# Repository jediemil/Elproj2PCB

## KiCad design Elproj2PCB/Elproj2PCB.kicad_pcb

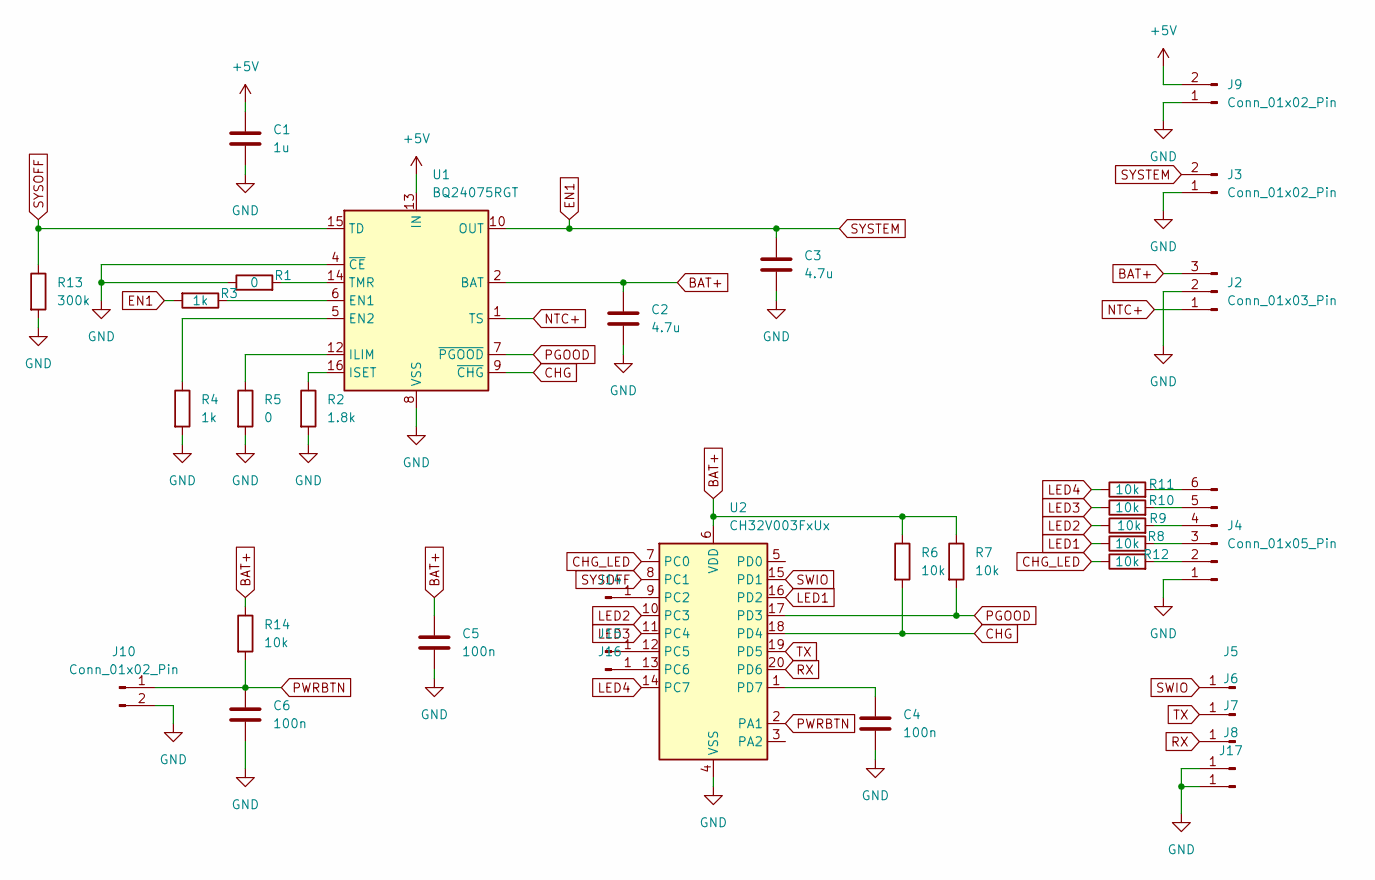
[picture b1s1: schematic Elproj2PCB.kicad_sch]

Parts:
C1: 1u; C_0603_1608Metric
C2, C3: 4.7u; C_0603_1608Metric
C4, C5, C6: 100n; C_0603_1608Metric
J2: Conn_01x03_Pin; PinHeader_1x03_P1.00mm_Vertical
J3, J9, J10: Conn_01x02_Pin; PinHeader_1x02_P1.00mm_Vertical
J4: Conn_01x05_Pin; PinHeader_1x06_P1.00mm_Vertical
J5, J6, J7, J8, J14, J15, J16, J17: Conn_01x01_Pin; TestPoint_Pad_D1.0mm
R1, R5: 0; R_0603_1608Metric
R2: 1.8k; R_0603_1608Metric
R3, R4: 1k; R_0603_1608Metric
R6, R7, R8, R9, R10, R11, R12, R14: 10k; R_0603_1608Metric
R13: 300k; R_0603_1608Metric
U1: BQ24075RGT; VQFN-16-1EP_3x3mm_P0.5mm_EP1.6x1.6mm
U2: CH32V003FxUx; QFN-20-1EP_3x3mm_P0.4mm_EP1.65x1.65mm

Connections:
+5V: C1.1, J9.2, U1.13 (IN)
BAT+: C2.1, C5.1, J2.3, R6.1, R7.1, R14.1, U1.2 (BAT), U1.3 (BAT), U2.6 (VDD)
CHG: R6.2, U1.9 (~CHG), U2.18 (PD4)
CHG_LED: R12.1, U2.7 (PC0)
EN1: C3.1, J3.2, R3.2, U1.10 (OUT), U1.11 (OUT)
GND: C1.2, C2.2, C3.2, C4.2, C5.2, C6.2, J2.2, J3.1, J4.1, J8.1, J9.1, J10.2, J17.1, R1.1, R2.2, R4.2, R5.2, R13.2, U1.4 (~CE), U1.8 (VSS), U1.17 (VSS), U2.4 (VSS), U2.21 (VSS)
LED1: R8.1, U2.16 (PD2)
LED2: R9.1, U2.10 (PC3)
LED3: R10.1, U2.11 (PC4)
LED4: R11.1, U2.14 (PC7)
NTC+: J2.1, U1.1 (TS)
unnamed: J4.2, R12.2
unnamed: J4.3, R8.2
unnamed: J4.4, R9.2
unnamed: J4.5, R10.2
unnamed: J4.6, R11.2
unnamed: J14.1, U2.9 (PC2)
unnamed: J15.1, U2.12 (PC5)
unnamed: J16.1, U2.13 (PC6)
unnamed: R3.1, U1.6 (EN1)
unnamed: R4.1, U1.5 (EN2)
unnamed: R5.1, U1.12 (ILIM)
unnamed: R2.1, U1.16 (ISET)
unnamed: R1.2, U1.14 (TMR)
unnamed: C4.1, U2.1 (PD7)
PGOOD: R7.2, U1.7 (~PGOOD), U2.17 (PD3)
PWRBTN: C6.1, J10.1, R14.2, U2.2 (PA1)
RX: J7.1, U2.20 (PD6)
SWIO: J5.1, U2.15 (PD1)
SYSOFF: R13.1, U1.15 (TD), U2.8 (PC1)
TX: J6.1, U2.19 (PD5)

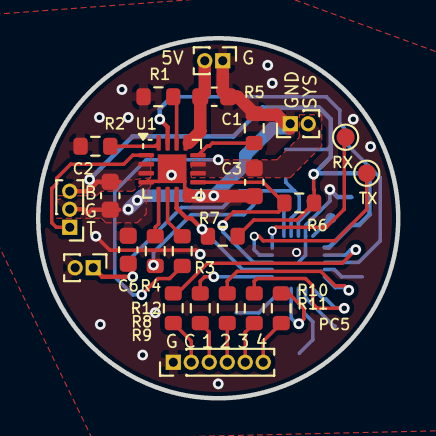
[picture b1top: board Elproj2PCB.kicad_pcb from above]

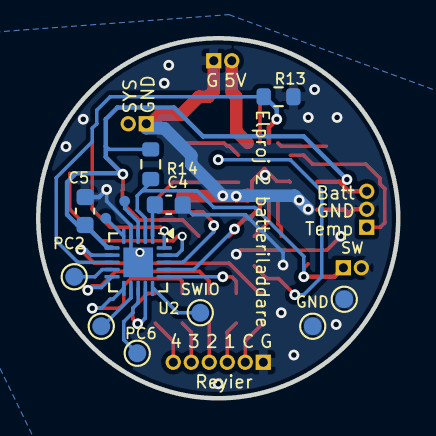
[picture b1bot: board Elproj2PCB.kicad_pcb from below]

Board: 2 copper layers, 20.0 x 20.0 mm, 35 parts (11 on the bottom side), 31 nets.

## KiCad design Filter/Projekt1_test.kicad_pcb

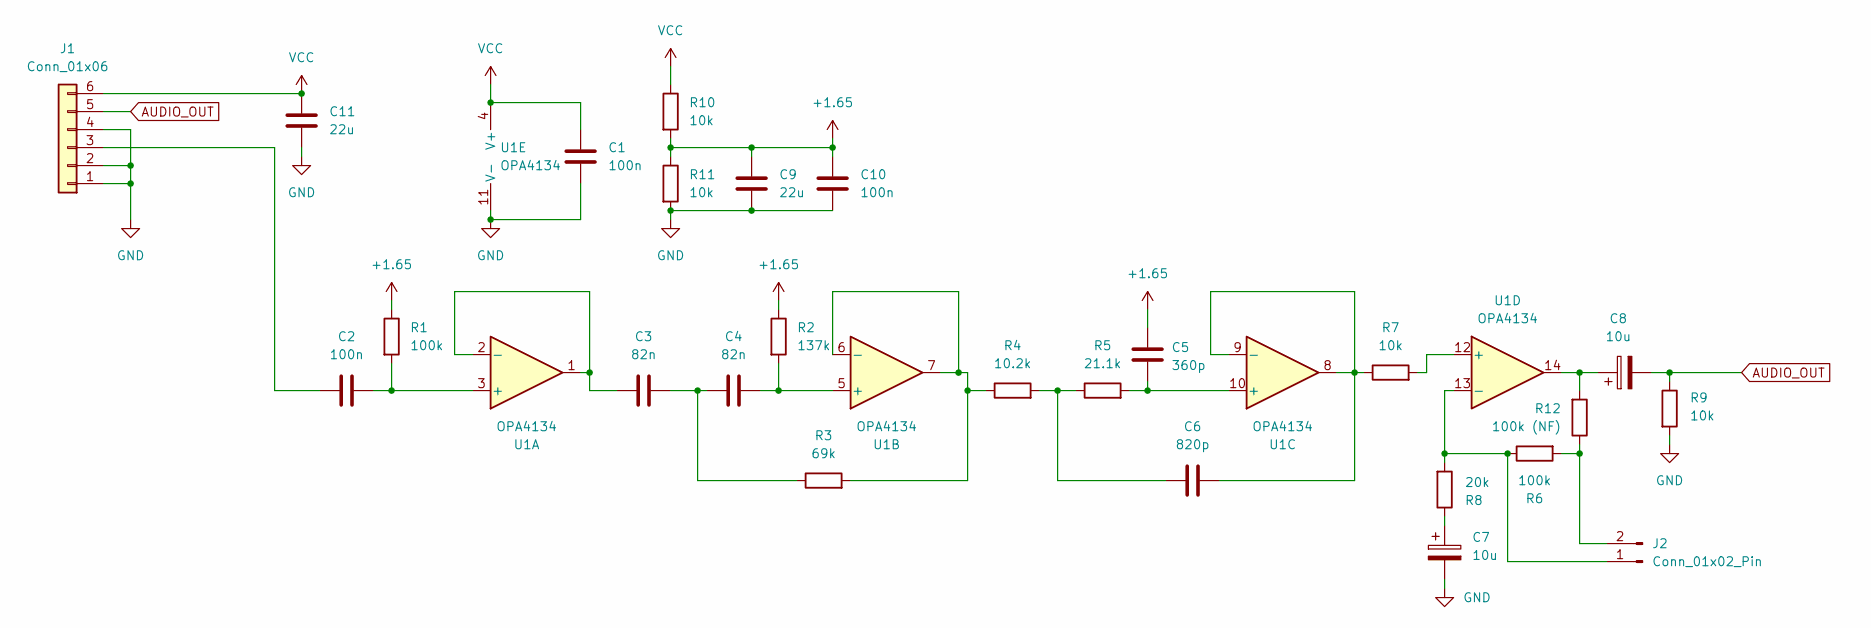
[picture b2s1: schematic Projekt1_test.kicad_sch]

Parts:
C1, C10: 100n; C_0603_1608Metric
C2: 100n; R_1206_3216Metric
C3, C4: 82n; R_1206_3216Metric
C5: 360p; R_1206_3216Metric
C6: 820p; R_1206_3216Metric
C7, C8: 10u; CP_EIA-3216-18_Kemet-A
C9, C11: 22u; C_0805_2012Metric
J1: Conn_01x06; PinHeader_1x06_P1.00mm_Vertical
J2: Conn_01x02_Pin; PinHeader_1x02_P1.00mm_Vertical
R1, R6: 100k; R_0603_1608Metric
R2: 137k; R_0603_1608Metric
R3: 69k; R_0603_1608Metric
R4: 10.2k; R_0603_1608Metric
R5: 21.1k; R_0603_1608Metric
R7, R9, R10, R11: 10k; R_0603_1608Metric
R8: 20k; R_0603_1608Metric
R12: 100k (NF); R_0603_1608Metric
U1: OPA4134; SOIC-14_3.9x8.7mm_P1.27mm

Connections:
+1.65: C5.2, C9.2, C10.2, R1.1, R2.1, R10.2, R11.1
AUDIO_OUT: C8.2, J1.5, R9.1
GND: C1.1, C7.2, C9.1, C10.1, C11.1, J1.1, J1.2, J1.4, R9.2, R11.2, U1.11 (V-)
unnamed: C3.1, C4.2, R3.1
unnamed: C6.2, R4.2, R5.1
unnamed: C7.1, R8.1
unnamed: C8.1, R12.2, U1.14
unnamed: C2.2, J1.3
unnamed: J2.1, R6.1, R8.2, U1.13 (-)
unnamed: J2.2, R6.2, R12.1
unnamed: C2.1, R1.2, U1.3 (+)
unnamed: C3.2, U1.1, U1.2 (-)
unnamed: C4.1, R2.2, U1.5 (+)
unnamed: R3.2, R4.1, U1.6 (-), U1.7
unnamed: C5.1, R5.2, U1.10 (+)
unnamed: C6.1, R7.1, U1.8, U1.9 (-)
unnamed: R7.2, U1.12 (+)
VCC: C1.2, C11.2, J1.6, R10.1, U1.4 (V+)

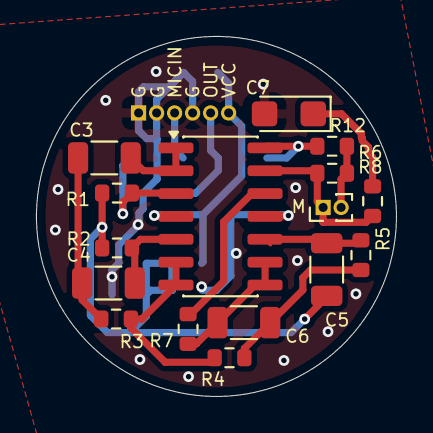
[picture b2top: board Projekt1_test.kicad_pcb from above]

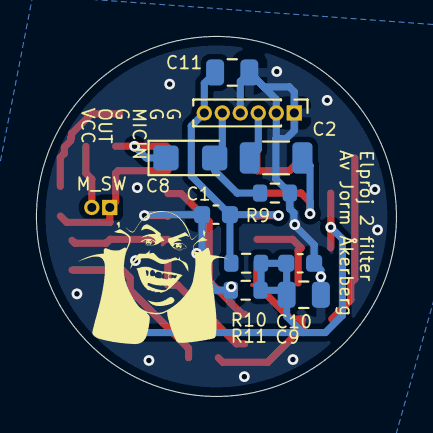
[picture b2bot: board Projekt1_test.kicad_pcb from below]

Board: 4 copper layers, 20.0 x 20.0 mm, 26 parts (10 on the bottom side), 18 nets.

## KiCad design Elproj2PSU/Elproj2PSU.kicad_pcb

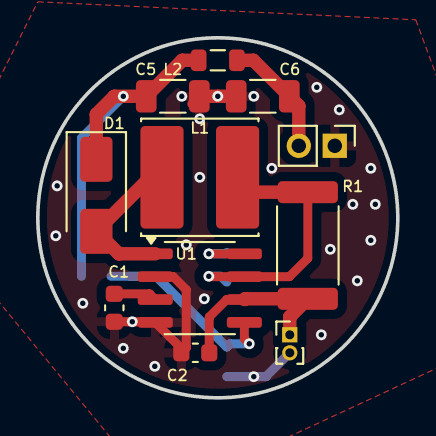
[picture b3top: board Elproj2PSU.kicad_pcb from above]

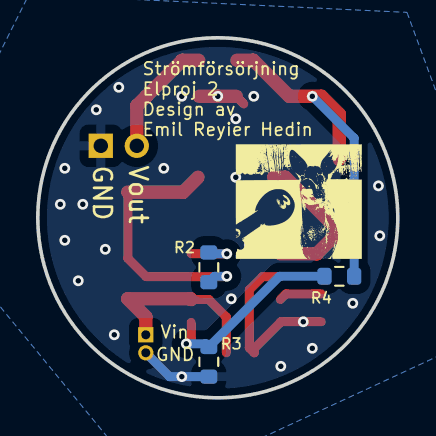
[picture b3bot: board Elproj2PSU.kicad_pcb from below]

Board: 2 copper layers, 20.0 x 20.0 mm, 14 parts (3 on the bottom side), 9 nets.

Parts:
C1: 400p; C_0603_1608Metric
C2: 100n; C_0603_1608Metric
C5, C6: 2.2u; C_1206_3216Metric
D1: D; D_SMA
J1: Conn_01x02_Pin; PinHeader_1x02_P1.00mm_Vertical
J2: Conn_01x02_Pin; PinHeader_1x02_P2.00mm_Vertical
L1: 78u; L_Cenker_CKCS6028
L2: 4.7u; L_0805_2012Metric
R1: 0.8; R_2512_6332Metric
R2: 180; R_0603_1608Metric
R3: 1.5k; R_0603_1608Metric
R4: 56k; R_0603_1608Metric
U1: MC34063AD; SOIC-8_3.9x4.9mm_P1.27mm

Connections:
+48V: C6.1, J2.2, L2.2
+BATT: C2.1, J1.1, R1.1, U1.6 (Vin)
GND: C1.2, C2.2, C5.2, C6.2, J1.2, J2.1, R3.1, U1.2 (SwE), U1.4 (GND)
unnamed: D1.2 (A), L1.2, U1.1 (SwC)
unnamed: C5.1, D1.1 (K), L2.1, R4.2
unnamed: R2.1, U1.8 (DC)
unnamed: L1.1, R1.2, R2.2, U1.7 (Ipk)
unnamed: C1.1, U1.3 (TC)
unnamed: R3.2, R4.1, U1.5 (Vfb)

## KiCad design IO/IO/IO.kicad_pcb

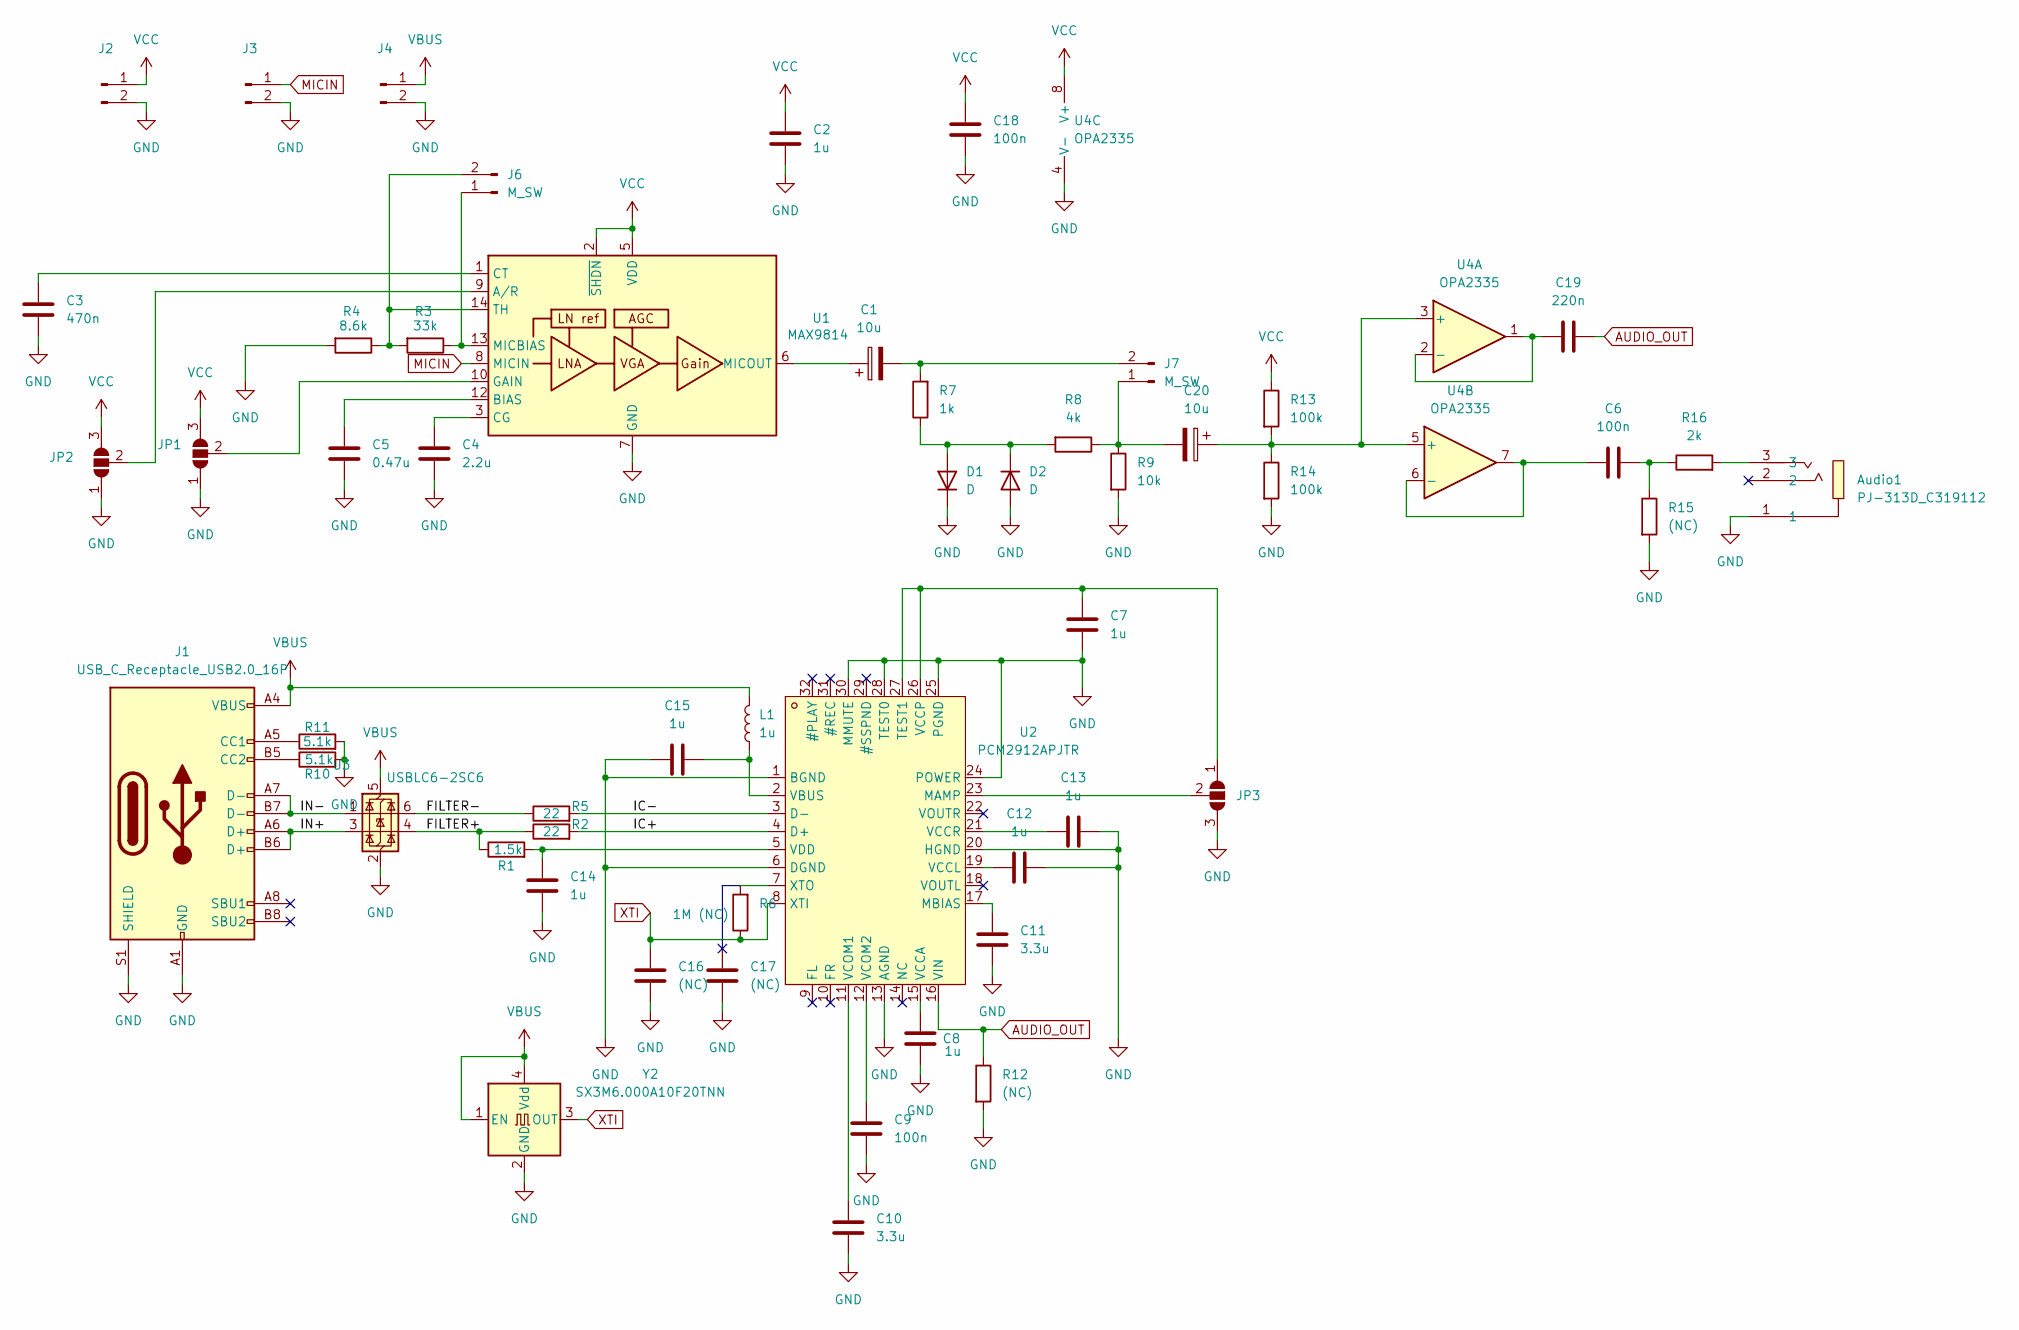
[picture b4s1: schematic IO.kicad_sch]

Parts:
Audio1: PJ-313D_C319112; AUDIO-TH_PJ-3135-B; LCSC Part C319112
C1, C20: 10u; CP_EIA-3216-18_Kemet-A
C2, C7, C8, C12, C13, C14, C15: 1u; C_0402_1005Metric
C3: 470n; C_0402_1005Metric
C4: 2.2u; C_0402_1005Metric
C5: 0.47u; C_0402_1005Metric
C6: 100n; R_1206_3216Metric
C9, C18: 100n; C_0402_1005Metric
C10, C11: 3.3u; C_0402_1005Metric
C16, C17: (NC); C_0402_1005Metric
C19: 220n; R_1206_3216Metric
D1, D2: D; D_SOD-123
J1: USB_C_Receptacle_USB2.0_16P; USB_C_Receptacle_GCT_USB4105-xx-A_16P_TopMnt_Horizontal
J2, J3, J4: Conn_01x02_Pin; PinHeader_1x02_P1.00mm_Vertical
J6, J7: M_SW; PinHeader_1x02_P1.00mm_Vertical
JP1, JP2, JP3: SolderJumper_3_Open; SolderJumper-3_P1.3mm_Open_RoundedPad1.0x1.5mm
L1: 1u; L_0603_1608Metric
R1: 1.5k; R_0402_1005Metric
R2, R5: 22; R_0402_1005Metric
R3: 33k; R_0402_1005Metric
R4: 8.6k; R_0402_1005Metric
R6: 1M (NC); R_0402_1005Metric
R7: 1k; R_0402_1005Metric
R8: 4k; R_0402_1005Metric
R9: 10k; R_0402_1005Metric
R10, R11: 5.1k; R_0402_1005Metric
R12, R15: (NC); R_0402_1005Metric
R13, R14: 100k; R_0402_1005Metric
R16: 2k; R_0402_1005Metric
U1: MAX9814; DFN-14-1EP_3x3mm_P0.4mm_EP1.78x2.35mm
U2: PCM2912APJTR; TQFP-32_L7.0-W7.0-P0.80-LS9.0-TL; LCSC Part C475497
U3: USBLC6-2SC6; SOT-23-6
U4: OPA2335; SOIC-8_3.9x4.9mm_P1.27mm
Y2: SX3M6.000A10F20TNN; Crystal_SMD_3225-4Pin_3.2x2.5mm

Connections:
/FILTER+: R1.1, R2.1, U3.4 (I/O2)
/FILTER-: R5.1, U3.6 (I/O1)
/IC+: R2.2, U2.4 (D+)
/IC-: R5.2, U2.3 (D-)
/IN+: J1.A6 (D+), J1.B6 (D+), U3.3 (I/O2)
/IN-: J1.A7 (D-), J1.B7 (D-), U3.1 (I/O1)
AUDIO_OUT: C19.2, R12.1, U2.16 (VIN)
GND: Audio1.1, C2.1, C3.1, C4.1, C5.1, C7.1, C8.1, C9.1, C10.1, C11.1, C12.1, C13.1, C14.2, C15.1, C16.1, C17.1, C18.1, D1.1 (K), D2.2 (A), J1.A1 (GND), J1.A12 (GND), J1.B1 (GND), J1.B12 (GND), J1.S1 (SHIELD), J2.2, J3.2, J4.2, JP1.1 (A), JP2.1 (A), JP3.3 (B), R4.2, R9.2, R10.2, R11.2, R12.2, R14.2, R15.2, U1.4 (GND), U1.7 (GND), U1.11 (GND), U1.15 (GND), U2.1 (BGND), U2.6 (DGND), U2.13 (AGND), U2.20 (HGND), U2.24 (POWER), U2.25 (PGND), U2.28 (TEST0), U2.30 (MMUTE), U3.2 (GND), U4.4 (V-), Y2.2 (GND)
MICIN: J3.1, U1.8 (MICIN)
unnamed: Audio1.3, R16.2
unnamed: C6.2, R15.1, R16.1
unnamed: D1.2 (A), D2.1 (K), R7.1, R8.2
unnamed: J1.A5 (CC1), R11.1
unnamed: J1.B5 (CC2), R10.1
unnamed: J6.1, R3.1, U1.13 (MICBIAS)
unnamed: J6.2, R3.2, R4.1, U1.14 (TH)
unnamed: C20.2, J7.1, R8.1, R9.1
unnamed: C1.2, J7.2, R7.2
unnamed: JP1.2 (C), U1.10 (GAIN)
unnamed: JP2.2 (C), U1.9 (A/R)
unnamed: C7.2, JP3.1 (A), U2.26 (VCCP), U2.27 (TEST1)
unnamed: JP3.2 (C), U2.23 (MAMP)
unnamed: C5.2, U1.12 (BIAS)
unnamed: C4.2, U1.3 (CG)
unnamed: C3.2, U1.1 (CT)
unnamed: C1.1, U1.6 (MICOUT)
unnamed: C11.2, U2.17 (MBIAS)
unnamed: C15.2, L1.1, U2.2 (VBUS)
unnamed: C8.2, U2.15 (VCCA)
unnamed: C12.2, U2.19 (VCCL)
unnamed: C13.2, U2.21 (VCCR)
unnamed: C10.2, U2.11 (VCOM1)
unnamed: C9.2, U2.12 (VCOM2)
unnamed: C14.1, R1.2, U2.5 (VDD)
unnamed: R6.2, U2.7 (XTO)
unnamed: C20.1, R13.2, R14.1, U4.3 (+), U4.5 (+)
unnamed: C19.1, U4.1, U4.2 (-)
unnamed: C6.1, U4.6 (-), U4.7
VBUS: J1.A4 (VBUS), J1.A9 (VBUS), J1.B4 (VBUS), J1.B9 (VBUS), J4.1, L1.2, U3.5 (VBUS), Y2.1 (EN), Y2.4 (Vdd)
VCC: C2.2, C18.2, J2.1, JP1.3 (B), JP2.3 (B), R13.1, U1.2 (~SHDN), U1.5 (VDD), U4.8 (V+)
XTI: C16.2, R6.1, U2.8 (XTI), Y2.3 (OUT)

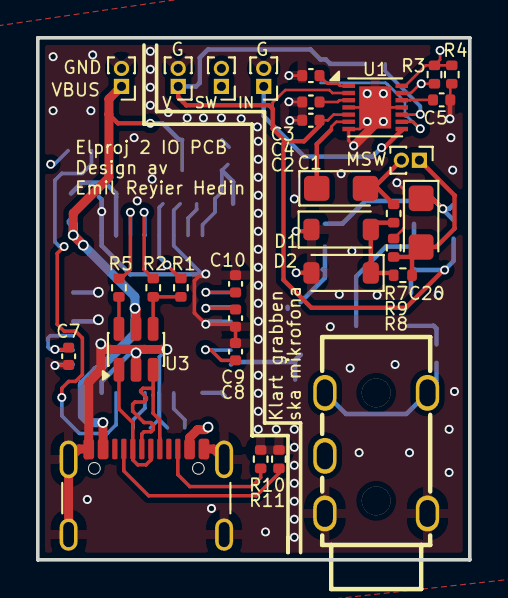
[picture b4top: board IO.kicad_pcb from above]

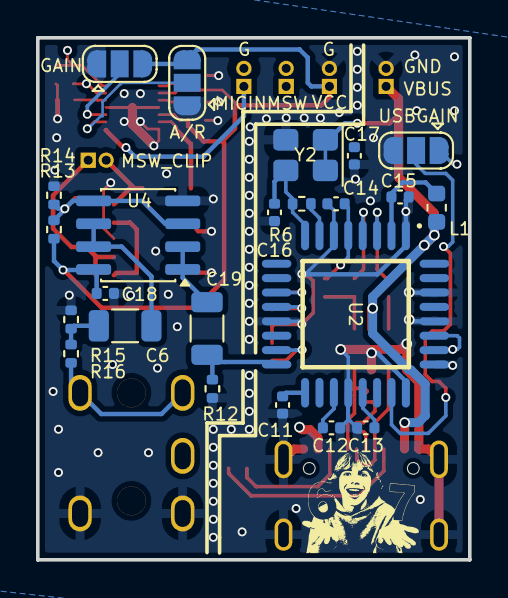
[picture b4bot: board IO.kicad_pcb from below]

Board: 4 copper layers, 24.0 x 29.0 mm, 54 parts (23 on the bottom side), 41 nets.

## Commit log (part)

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2025-12-30 Först
2025-12-31 Mer jobb
2026-01-12 Kopplingsschema klart? och påbörjad layout
2026-01-12 Klar IO? och förstört jorms kretskort
2026-01-12 Snart klar med allt? Jorms kretskort är lagat
2026-01-13 Final fixes
2026-01-13 Generera gbr
2026-01-22 Add 3d
2026-02-13 Lägg till membran
